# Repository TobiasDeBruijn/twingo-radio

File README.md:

# Twingo Radio

Software for the Arduino managing the infotainment system in my Renault Twingo.

## Hardware setup
I replaced the factory FM-radio with an Android Auto setup.
The setup is powered by a raspberry pi 4 running Crankshaft-NG.
Together with an Arduino and four relays. While I eventually want to create
a PCB for this setup, it's currently hand-soldered underneath the driver's seat.

I used a tablet holder to bolt a 7.5" display to my dashboard.
Inside the old place for the radio is a USB hub for the touch screen, 
a USB microphone, an AA-Wireless dongle and a USB cable for wired AA.
This USB hub needs to be powered, otherwhise AA will be very unstable if used wired.

There are four relays:
- Car remote detect
- Amplifier
- Main power relay
- Secondary power relay

### Car remote detect
This relay simply steps down the car's 12V remote signal, which was originally connected to the radio,
to a 3.3V signal, which is fed into the Arduino

### Amplifier
Switches on the speaker amplifier

### Main power relay
Switched by the car's 12V remote signal, turns on the 12V supply to the DC-DC converter

### Secondary power relay
Switched by the Arduino, also turns on the 12V supply to the DC-DC converter.
Used to supply power a little bit longer than the car's power off. This avoids
a 'plop' sound on the speakers. The amplifier is turned off a little bit before the Arduino
turns off this relay

### IO with the Pi
- Volume up
- Volume down
- Track next
- Track prev
- Mute pin
- Pi ready pin

### Pi Ready pin
Activated by the Pi with a startup script. Informs the Arduino the system is booted and the
amplifier can be turned on.

## Integration with the steering wheel
The Twingo has some buttons on the steering wheel to control the volume, source, etc.
The controls are hooked up to the Arduino so it can be used with Android Auto.

# License

MIT or Apache-2.0, at your option

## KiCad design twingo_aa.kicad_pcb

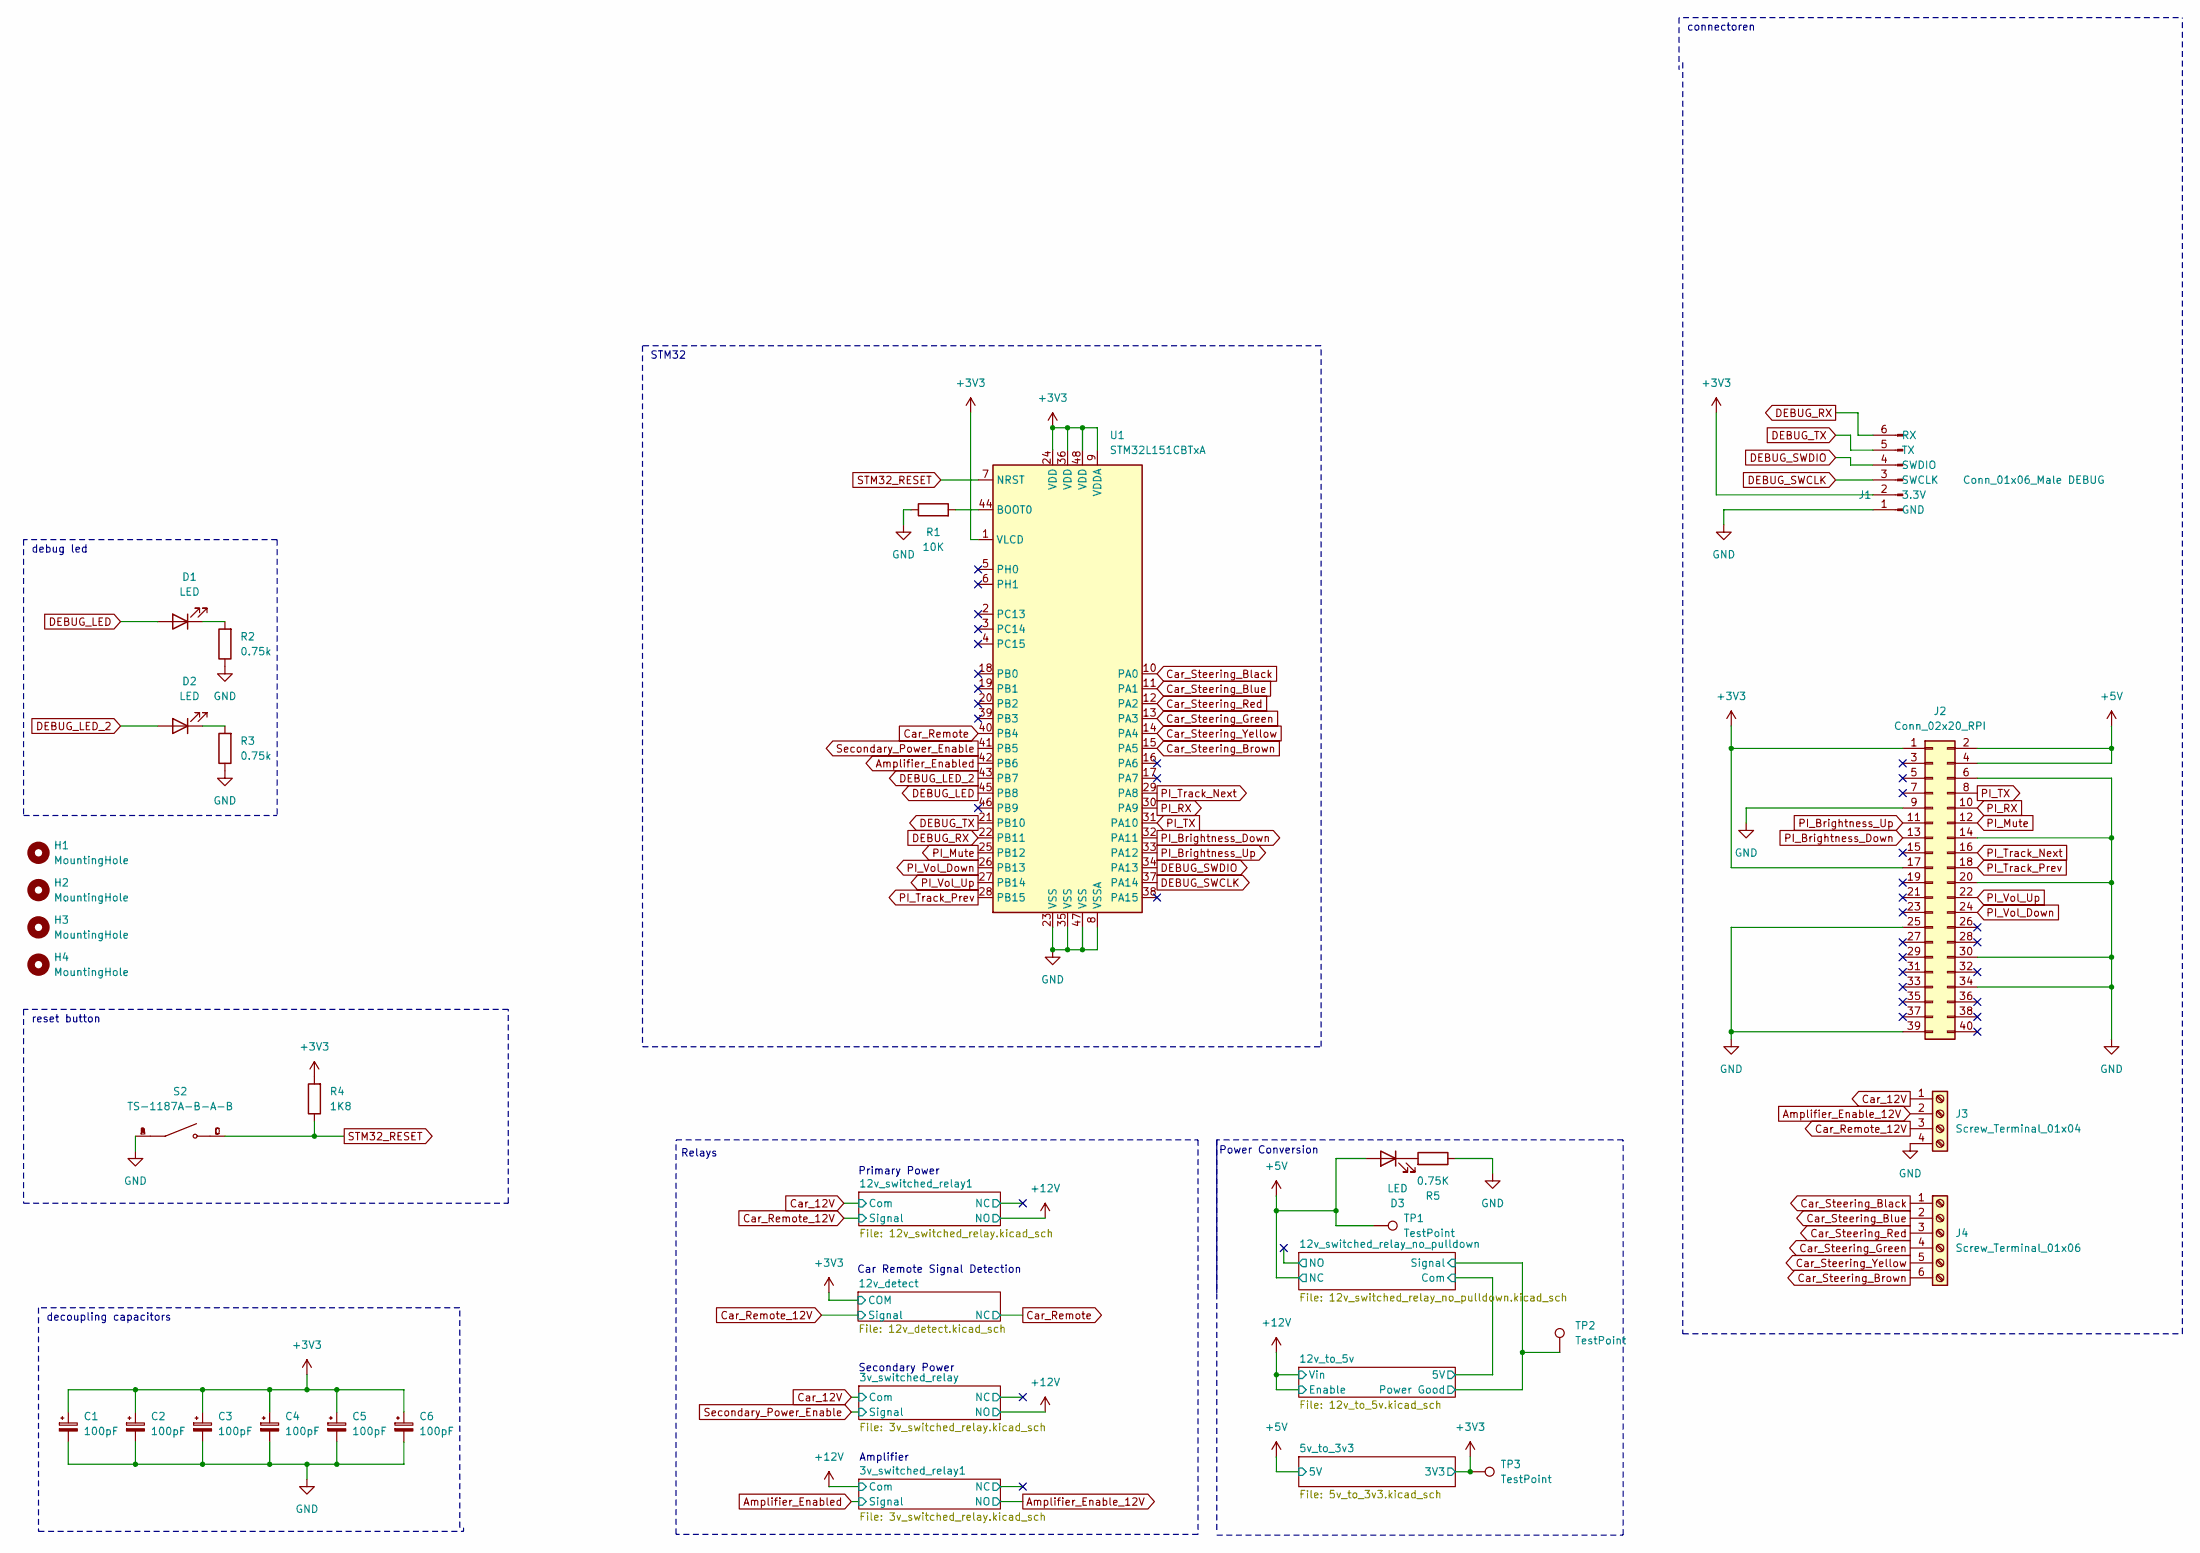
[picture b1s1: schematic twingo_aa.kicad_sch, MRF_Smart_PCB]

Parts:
C1, C2, C3, C4, C5, C6: 100pF; C_0805_2012Metric
D1, D2, D3: LED; LED_0805_2012Metric
H1, H2, H3, H4: MountingHole; MountingHole_2.5mm
J1: Conn_01x06_Male DEBUG; JST_SHL_SM06B-SHLS-TF_1x06-1MP_P1.00mm_Horizontal
J2: Conn_02x20_RPI; PinSocket_2x20_P2.54mm_Vertical
J3: Screw_Terminal_01x04; TerminalBlock_bornier-4_P5.08mm
J4: Screw_Terminal_01x06; TerminalBlock_bornier-6_P5.08mm
R1: 10K; R_1206_3216Metric
R2, R3: 0.75k; R_0603_1608Metric
R4: 1K8; R_0603_1608Metric
R5: 0.75K; R_0805_2012Metric
S2: TS-1187A-B-A-B; SW_TS-1187A-B-A-B; PARTREV A0
TP1, TP2, TP3: TestPoint; TestPoint_Pad_D1.0mm
U1: STM32L151CBTxA; LQFP-48_7x7mm_P0.5mm

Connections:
+3V3: C1.1, C2.1, C3.1, C4.1, C5.1, C6.1, J1.2 (3.3V), J2.1, J2.17, R4.2, TP3.1, U1.1 (VLCD), U1.9 (VDDA), U1.24 (VDD), U1.36 (VDD), U1.48 (VDD); also elsewhere on the board
+5V: D3.2 (A), J2.2, J2.4, TP1.1; also elsewhere on the board
/12v_switched_relay_no_pulldown/Signal: TP2.1; also elsewhere on the board
Amplifier_Enable_12V: J3.2; also elsewhere on the board
Amplifier_Enabled: U1.42 (PB6); also elsewhere on the board
Car_12V: J3.1; also elsewhere on the board
Car_Remote: U1.40 (PB4); also elsewhere on the board
Car_Remote_12V: J3.3; also elsewhere on the board
Car_Steering_Black: J4.1, U1.10 (PA0)
Car_Steering_Blue: J4.2, U1.11 (PA1)
Car_Steering_Brown: J4.6, U1.15 (PA5)
Car_Steering_Green: J4.4, U1.13 (PA3)
Car_Steering_Red: J4.3, U1.12 (PA2)
Car_Steering_Yellow: J4.5, U1.14 (PA4)
DEBUG_LED: D1.2 (A), U1.45 (PB8)
DEBUG_LED_2: D2.2 (A), U1.43 (PB7)
DEBUG_RX: J1.6 (RX), U1.22 (PB11)
DEBUG_SWCLK: J1.3 (SWCLK), U1.37 (PA14)
DEBUG_SWDIO: J1.4 (SWDIO), U1.34 (PA13)
DEBUG_TX: J1.5 (TX), U1.21 (PB10)
GND: C1.2, C2.2, C3.2, C4.2, C5.2, C6.2, J1.1 (GND), J2.6, J2.9, J2.14, J2.20, J2.25, J2.30, J2.34, J2.39, J3.4, R1.1, R2.1, R3.1, R5.1, S2.A, S2.B, U1.8 (VSSA), U1.23 (VSS), U1.35 (VSS), U1.47 (VSS); also elsewhere on the board
unnamed: D1.1 (K), R2.2
unnamed: D2.1 (K), R3.2
unnamed: D3.1 (K), R5.2
unnamed: R1.2, U1.44 (BOOT0)
PI_Brightness_Down: J2.13, U1.32 (PA11)
PI_Brightness_Up: J2.11, U1.33 (PA12)
PI_Mute: J2.12, U1.25 (PB12)
PI_RX: J2.10, U1.30 (PA9)
PI_TX: J2.8, U1.31 (PA10)
PI_Track_Next: J2.16, U1.29 (PA8)
PI_Track_Prev: J2.18, U1.28 (PB15)
PI_Vol_Down: J2.24, U1.26 (PB13)
PI_Vol_Up: J2.22, U1.27 (PB14)
STM32_RESET: R4.1, S2.C, S2.D, U1.7 (NRST)
Secondary_Power_Enable: U1.41 (PB5); also elsewhere on the board

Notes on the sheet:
decoupling capacitors
Relays
Amplifier
Car Remote Signal Detection
Secondary Power
Power Conversion
debug led
STM32
Primary Power
reset button
connectoren

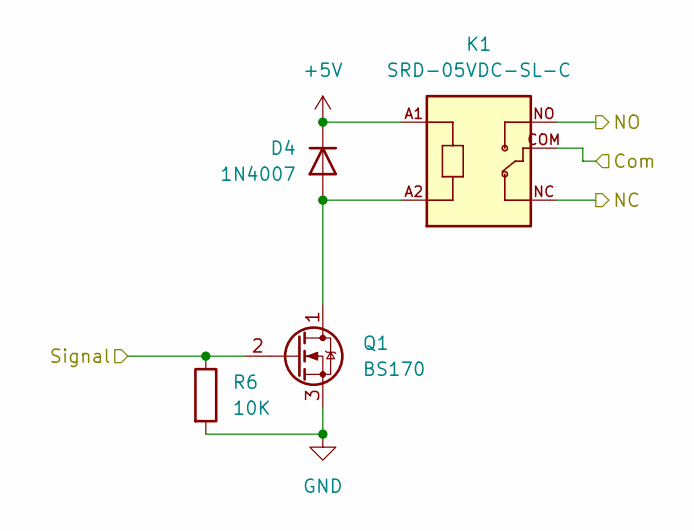
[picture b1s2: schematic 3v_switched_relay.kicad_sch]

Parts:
D4: 1N4007; D_DO-41_SOD81_P10.16mm_Horizontal
K1: SRD-05VDC-SL-C; RELAY_SRD-05VDC-SL-C
Q1: BS170; TO-92_Inline
R6: 10K; R_1206_3216Metric

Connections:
+5V: D4.1 (K), K1.A1; also elsewhere on the board
+12V: K1.NO; also elsewhere on the board
/3v_switched_relay/NC: K1.NC
Car_12V: K1.COM; also elsewhere on the board
GND: Q1.3 (S), R6.2; also elsewhere on the board
unnamed: D4.2 (A), K1.A2, Q1.1 (D)
Secondary_Power_Enable: Q1.2 (G), R6.1; also elsewhere on the board

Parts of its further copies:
D5: 1N4007; D_DO-41_SOD81_P10.16mm_Horizontal
K2: SRD-05VDC-SL-C; RELAY_SRD-05VDC-SL-C
Q2: BS170; TO-92_Inline
R7: 10K; R_1206_3216Metric

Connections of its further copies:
+5V: D5.1 (K), K2.A1; also elsewhere on the board
+12V: K2.COM; also elsewhere on the board
/3v_switched_relay1/NC: K2.NC
Amplifier_Enable_12V: K2.NO; also elsewhere on the board
Amplifier_Enabled: Q2.2 (G), R7.1; also elsewhere on the board
GND: Q2.3 (S), R7.2; also elsewhere on the board
unnamed: D5.2 (A), K2.A2, Q2.1 (D)

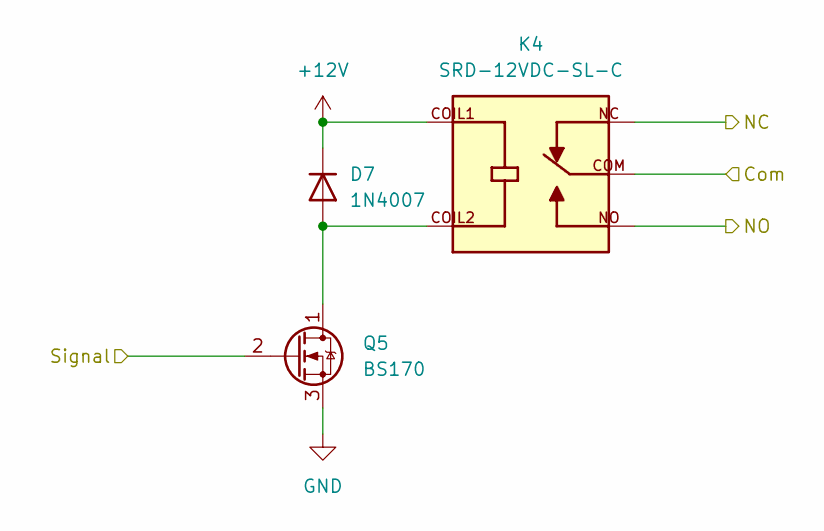
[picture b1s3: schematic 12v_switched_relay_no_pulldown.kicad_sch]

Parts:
D7: 1N4007; D_DO-41_SOD81_P10.16mm_Horizontal
K4: SRD-12VDC-SL-C; RELAY_SRD-12VDC-SL-C; PARTREV 1.0
Q5: BS170; TO-92_Inline

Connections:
+5V: K4.NC; also elsewhere on the board
+12V: D7.1 (K), K4.COIL1; also elsewhere on the board
/12v_switched_relay_no_pulldown/Com: K4.COM; also elsewhere on the board
/12v_switched_relay_no_pulldown/NO: K4.NO
/12v_switched_relay_no_pulldown/Signal: Q5.2 (G); also elsewhere on the board
GND: Q5.3 (S); also elsewhere on the board
unnamed: D7.2 (A), K4.COIL2, Q5.1 (D)

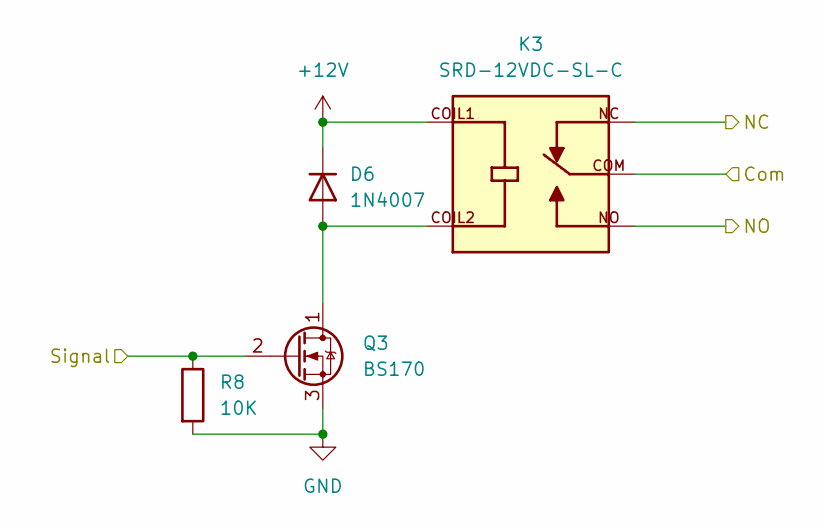
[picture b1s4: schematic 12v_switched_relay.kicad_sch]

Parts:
D6: 1N4007; D_DO-41_SOD81_P10.16mm_Horizontal
K3: SRD-12VDC-SL-C; RELAY_SRD-12VDC-SL-C; PARTREV 1.0
Q3: BS170; TO-92_Inline
R8: 10K; R_1206_3216Metric

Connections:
+12V: D6.1 (K), K3.COIL1, K3.NO; also elsewhere on the board
/12v_switched_relay1/NC: K3.NC
Car_12V: K3.COM; also elsewhere on the board
Car_Remote_12V: Q3.2 (G), R8.1; also elsewhere on the board
GND: Q3.3 (S), R8.2; also elsewhere on the board
unnamed: D6.2 (A), K3.COIL2, Q3.1 (D)

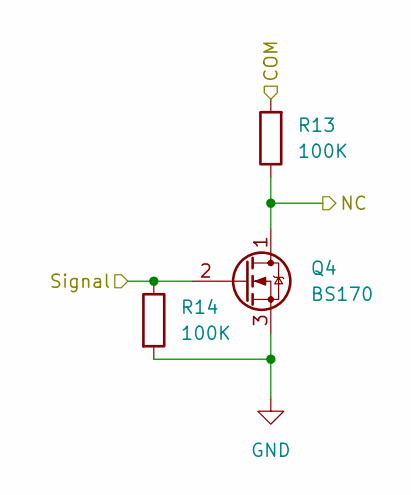
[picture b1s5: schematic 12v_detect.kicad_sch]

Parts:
Q4: BS170; TO-92_Inline
R13, R14: 100K; R_1206_3216Metric

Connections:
+3V3: R13.2; also elsewhere on the board
Car_Remote: Q4.1 (D), R13.1; also elsewhere on the board
Car_Remote_12V: Q4.2 (G), R14.1; also elsewhere on the board
GND: Q4.3 (S), R14.2; also elsewhere on the board

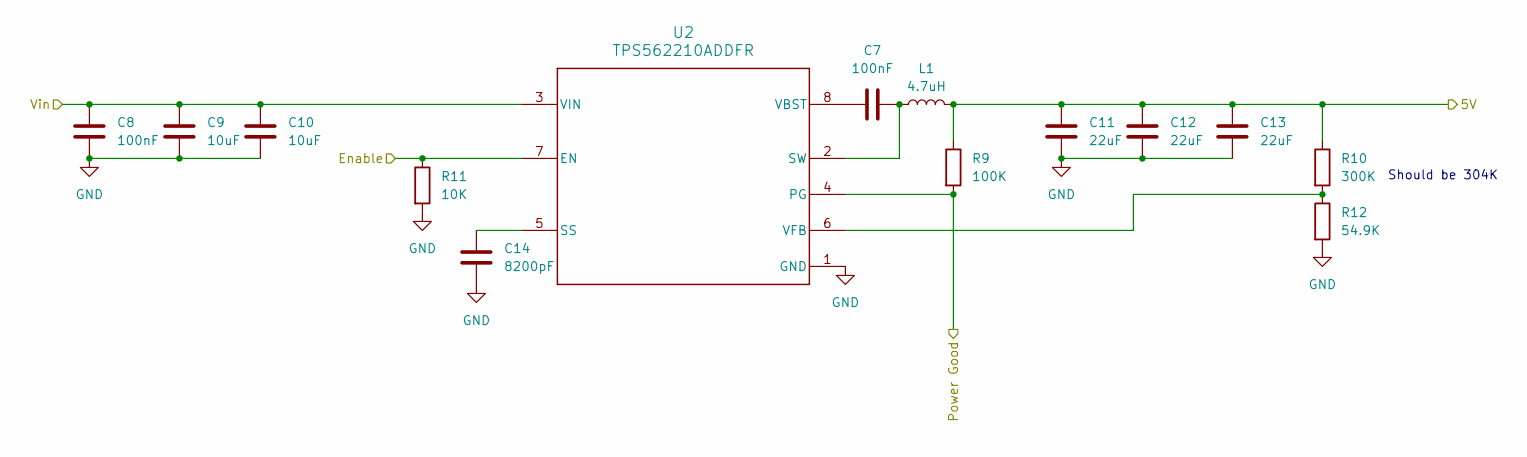
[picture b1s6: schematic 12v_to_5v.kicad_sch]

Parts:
C7, C8: 100nF; C_0402_1005Metric
C9, C10: 10uF; C_1206_3216Metric
C11, C12, C13: 22uF; C_1206_3216Metric
C14: 8200pF; C_0603_1608Metric
L1: 4.7uH; L_1206_3216Metric
R9: 100K; R_1206_3216Metric
R10: 300K; R_0603_1608Metric
R11: 10K; R_1206_3216Metric
R12: 54.9K; R_0402_1005Metric
U2: TPS562210ADDFR; TPS562210A_N

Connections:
+12V: C8.1, C9.1, C10.1, R11.1, U2.3 (VIN), U2.7 (EN); also elsewhere on the board
/12v_switched_relay_no_pulldown/Com: C11.2, C12.2, C13.2, L1.2, R9.1, R10.1; also elsewhere on the board
/12v_switched_relay_no_pulldown/Signal: R9.2, U2.4 (PG); also elsewhere on the board
GND: C8.2, C9.2, C10.2, C11.1, C12.1, C13.1, C14.2, R11.2, R12.2, U2.1 (GND); also elsewhere on the board
unnamed: C14.1, U2.5 (SS)
unnamed: C7.2, L1.1, U2.2 (SW)
unnamed: C7.1, U2.8 (VBST)
unnamed: R10.2, R12.1, U2.6 (VFB)

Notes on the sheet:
Should be 304K

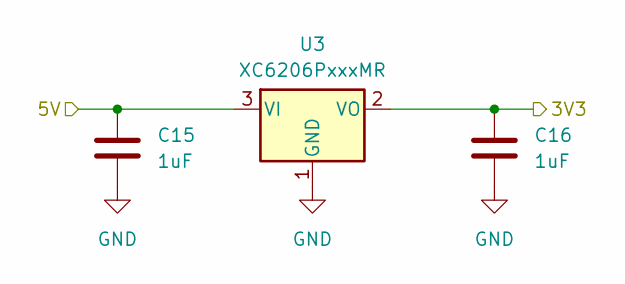
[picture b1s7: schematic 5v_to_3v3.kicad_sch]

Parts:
C15, C16: 1uF; C_1206_3216Metric
U3: XC6206PxxxMR; SOT-23-3

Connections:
+3V3: C16.1, U3.2 (VO); also elsewhere on the board
+5V: C15.1, U3.3 (VI); also elsewhere on the board
GND: C15.2, C16.2, U3.1 (GND); also elsewhere on the board

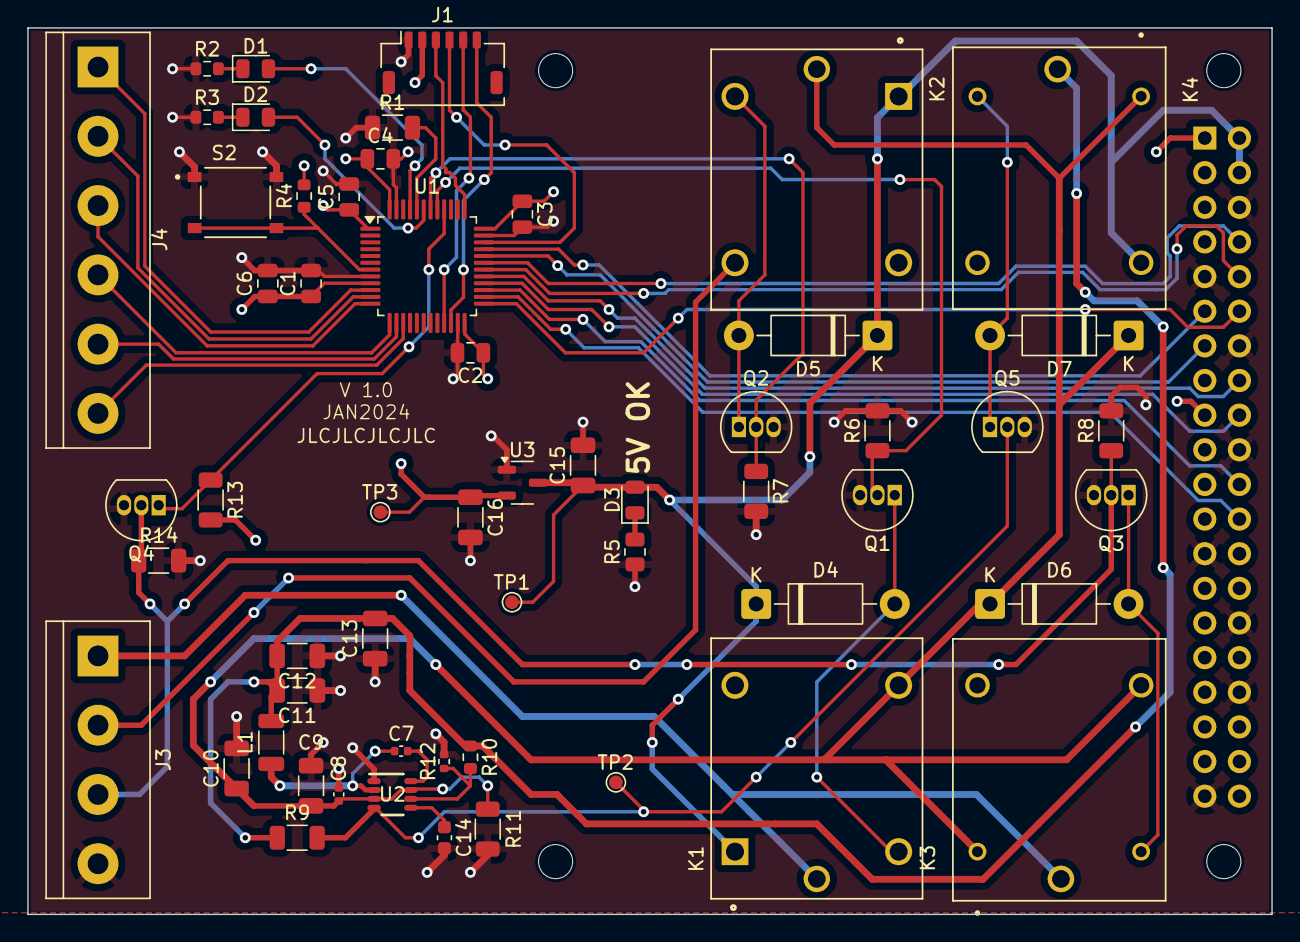
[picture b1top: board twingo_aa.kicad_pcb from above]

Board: 4 copper layers, 91.2 x 65.0 mm, 62 parts (1 on the bottom side), 46 nets.

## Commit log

2023-08-24 Fixed volume
2023-10-16 Track forward & back; Mute button
2024-07-28 Update for new project
2024-07-28 remove delay in loop
2025-02-09 Rework car remote detection
2025-02-09 Fix: flaky Pi-ready signal Add readme
2025-07-28 Various fixes
2025-07-28 Most of the layout completed
